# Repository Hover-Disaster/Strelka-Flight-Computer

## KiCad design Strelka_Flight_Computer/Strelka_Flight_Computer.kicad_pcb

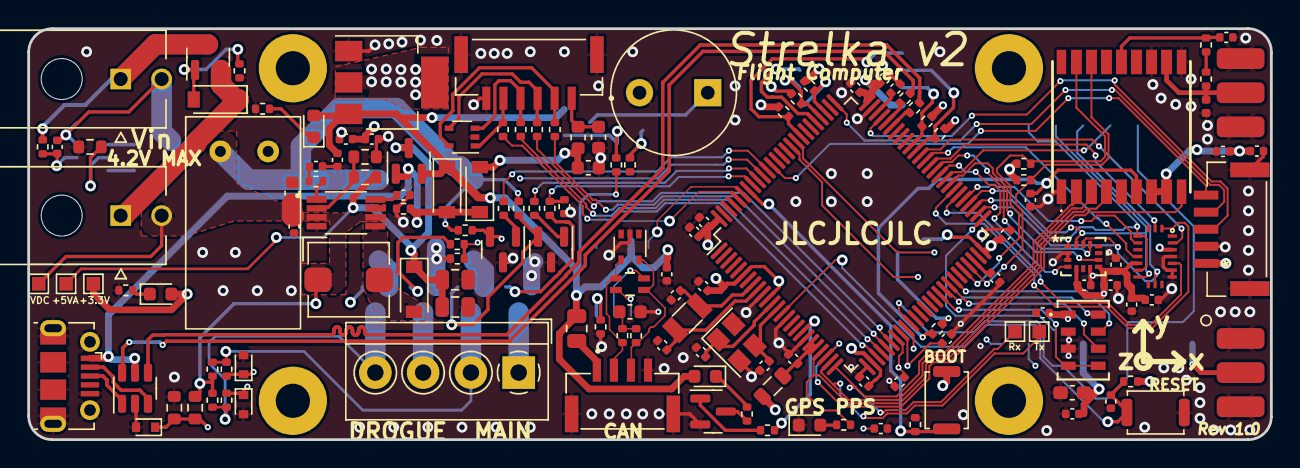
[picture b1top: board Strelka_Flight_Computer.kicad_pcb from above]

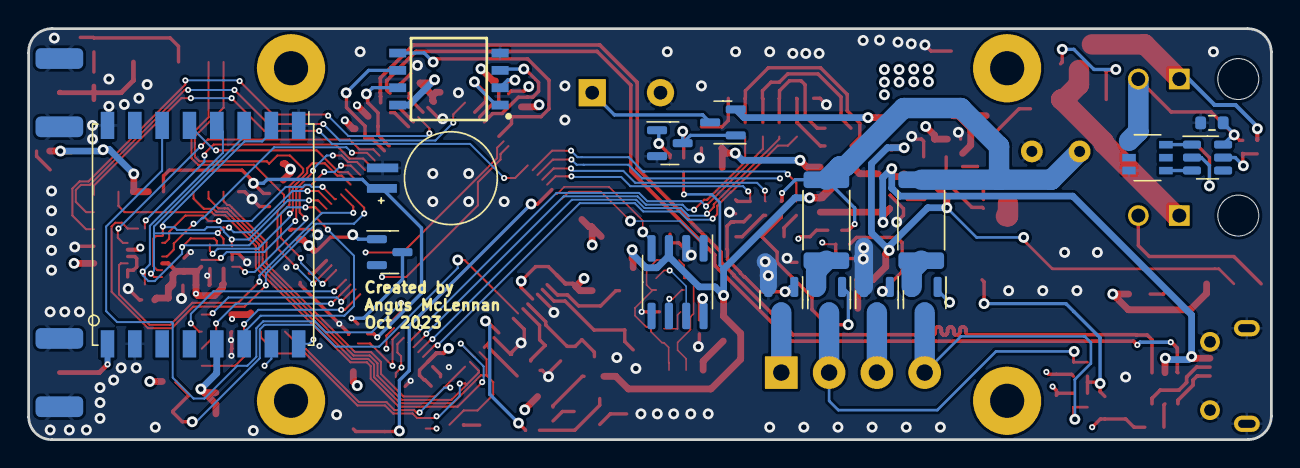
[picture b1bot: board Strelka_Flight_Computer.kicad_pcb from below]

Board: 4 copper layers, 91.0 x 30.1 mm, 165 parts (16 on the bottom side), 124 nets.

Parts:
AE1, AE2: Antenna_Shield; STA-10201
BT2: MS621FE-FL11E; BAT_MS621FE-FL11E
BZ3: Buzzer; HNB09A05
C1, C2, C4, C5, C6, C10, C28, C29, C30, C31, C39, C48, C50, C52, C53, C54, C60, C61, C66: 100n; C_0402_1005Metric
C3, C7, C8, C40: 10u; C_0402_1005Metric
C9, C12, C13: 10n; C_0402_1005Metric
C11: 10u; C_0603_1608Metric_Pad1.08x0.95mm_HandSolder
C14, C55: 22u; C_0805_2012Metric
C15: 4.7n; C_0603_1608Metric
C26, C27: 2.2u; C_0603_1608Metric
C37: NC; C_0402_1005Metric
C38: 4.7u; C_0402_1005Metric
C41: 1500u; ULR158M0JF1ARR
C46: 22u; C_0603_1608Metric
C47, C49: 1u; C_0402_1005Metric
C51: 2.2n; C_0402_1005Metric
C62, C63: 18p; C_0402_1005Metric
C64, C65: 15p; C_0402_1005Metric
C67, C68: 2.2u; C_0402_1005Metric
D1, D2, D4: B5819W; D_SOD-123
D3, D5, D13: BZT52C3V6T; D_SOD-523
D6, D7: SP0504BAJT; SOT-353_SC-70-5
D10: ESD9B3.3ST5G; D_0402_1005Metric
D11: BAT54C; SOT-23
D12: LED_GREEN; LED_0603_1608Metric
D14: DSK34; D_SOD-123
D18: RED LED; LED_0603_1608Metric
D19: YELLOW LED; LED_0603_1608Metric
D20: BLUE LED; LED_0603_1608Metric
F1: MF-PSHT035KX-2; R_0805_2012Metric
FB2: BLM18PG221SN1D; L_0603_1608Metric
FB3: HZ1005K182TFB03; R_0402_1005Metric
FL1: 744231121; CHIP_31121_WRE
H1, H2, H3, H4: MountingHole; MountingHole_2.5mm_Pad
IC1: XTSD04GLGEAG; SON127P800X600X95-8N
IC2: MAX-M10S-00B; MAXM10S00B
J2: Conn_01x04; JST_SM04B-GHS-TB(LF)(SN)-
J3: DB125-3.5-4P-GN-S; TerminalBlock_4Ucon_1x04_P3.50mm_Horizontal
J4: SM06B-GHS-TB(LF)(SN); JST_SM06B-GHS-TB(LF)(SN)
J6: USB_B_Micro; USB_Micro-B_Molex-105017-0001
J7: Conn_01x02; MOLEX_43045-0200
J8: Conn_01x07; SM05B-GHS-TBLFSN
L2: 6u; L_Bourns_SRP5030T
L4: 10u; L_0805_2012Metric
MOSFET1: DMG6968UDM-7
Q1, Q2: CJK2333; SOT-23
Q4, Q9, Q17: AO3401A; SOT-23
Q5, Q10: AP2300; SOT-23
Q6, Q11: MMBT2222; SOT-23
Q15, Q16: AO3400A; SOT-23
R1: 0R; R_0603_1608Metric
R2, R3, R4, R5, R6, R8, R81: 100k; R_0402_1005Metric
R7: 330R; R_0402_1005Metric
R9: 2.7k; R_0603_1608Metric
R10, R11, R12, R16, R17, R31, R51, R56, R57, R74, R77, R78, R80: 1k; R_0402_1005Metric
R13, R26: 60R4; R_0402_1005Metric
R14, R15, R61, R75, R79, R86, R87: 10k; R_0402_1005Metric
R18, R19, R21, R65, R76: 33R; R_0402_1005Metric
R20, R23, R24, R25, R35: 47k; R_0402_1005Metric
R22, R84: 10R; R_0402_1005Metric
R27, R47: 2R; R_2512_6332Metric
R55: 0R; R_0402_1005Metric
R59: 13k; R_0603_1608Metric
R60: 47k; R_0603_1608Metric
R62: 82k; R_0603_1608Metric
R63: 27k; R_0603_1608Metric
SW1: SW_DIP_x01; MOLEX_43045-0200
SW6, SW7: TS-1185-C-A-A-A; SW_Push_SPST_NO_Alps_SKRK
TP1, TP3, TP4, TP9, TP10: TestPoint; TestPoint_Pad_1.0x1.0mm
U1: ASM330LHHXTR; QFN_LHHXTR_STM
U2: AP9101CK6; SOT-23-6
U3: AMS1117-3.3; SOT-223-3_TabPin2
U4: RFM95W-915S2; HOPERF_RFM9XW_SMD
U5: MCP2551-I-SN; SOIC-8_3.9x4.9mm_P1.27mm
U6: STM32H743VITx; LQFP-100_14x14mm_P0.5mm
U8: USBLC6-2SC6; SOT-23-6
U11: BMX055
U12: MS561101BA03-50
U16: TPS61085DGKR; SOP65P490X110-8N
Y5: Q13FC1350000400; Crystal_SMD_3215-2Pin_3.2x1.5mm
Y6: X1E0000210834; Crystal_SMD_SeikoEpson_TSX3225-4Pin_3.2x2.5mm

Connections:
+3.3V: C2.1, C3.1, C4.1, C7.1, C8.1, C10.1, C11.1, C28.1, C29.1, C30.1, C31.1, C39.1, C40.1, C50.1, C52.1, C53.1, C54.1, C60.1, C61.1, D11.1, D19.2 (A), IC1.8 (VDD,_POWER_SUPPLY), IC2.7 (V_IO), IC2.8 (VCC), J8.1, L4.1, R20.1, R23.1, R24.1, R25.1, R35.1, R79.2, R86.2, R87.2, SW6.2, TP4.1, U1.5 (Vdd_IO), U1.8 (Vdd), U3.2 (VO), U4.13 (3.3V), U6.6 (VBAT), U6.11 (VDD), U6.27 (VDD), U6.50 (VDD), U6.75 (VDD), U6.100 (VDD), U11.3 (VDD), U11.13 (VDDIO), U12.1 (VDD)
+5V: C1.1, C5.1, D2.1 (K), D18.2 (A), D20.2 (A), F1.1, Q2.2 (S), Q17.2 (S), R81.2, U3.3 (VI), U5.3 (VDD)
+5VA: C14.1, C55.1, D14.1 (K), Q2.3 (D), R62.2, TP3.1
+5VD: C26.2, D4.2 (A), FB2.2
+BATT: J7.1, Q1.3 (D), R7.1
-BATT: C6.2, J7.2, MOSFET1.1 (S1), R1.1, U2.6 (VSS)
/915MHz_Radio/CS_RF: U4.5 (NSS), U6.59 (PD12)
/915MHz_Radio/IO0_RF: U4.14 (DIO0), U6.51 (PB12)
/915MHz_Radio/IO1_RF: U4.15 (DIO1), U6.84 (PD3)
/915MHz_Radio/IO2_RF: U4.16 (DIO2), U6.85 (PD4)
/915MHz_Radio/LoRa_Sig: AE1.1 (A), U4.9 (ANT)
/915MHz_Radio/RESET_RF: U4.6 (RESET), U6.35 (PB1)
/915MHz_Radio/SPI_CLK: U1.13 (SCL), U4.4 (SCK), U6.52 (PB13), U11.9 (SCX)
/915MHz_Radio/SPI_MISO: U1.1 (SDO/SA0), U4.2 (MISO), U6.53 (PB14), U11.12 (SDO2), U11.17 (SDO1)
/915MHz_Radio/SPI_MOSI: U1.14 (SDA), U4.3 (MOSI), U6.54 (PB15), U11.11 (SDX)
/Actuators/D+: J3.4, Q4.3 (D), R14.2, R16.2
/Actuators/D-: J3.3, Q5.3 (D)
/Actuators/DROGUE_CONT: C12.1, D3.1 (K), R14.1, U6.33 (PC5)
/Actuators/DROGUE_H: R10.1, U6.90 (PB4)
/Actuators/DROGUE_L: R5.2, R31.1, U6.91 (PB5)
/Actuators/EXT_SPI_CS: R21.2, U6.28 (PA4)
/Actuators/EXT_SPI_MISO: R65.2, U6.30 (PA6)
/Actuators/EXT_SPI_MOSI: R18.2, U6.31 (PA7)
/Actuators/EXT_SPI_SCK: R19.2, U6.29 (PA5)
/Actuators/Ematch_Drogue1/em+: Q4.2 (S), R27.2
/Actuators/Ematch_Main/em+: Q9.2 (S), R47.2
/Actuators/M+: J3.2, Q9.3 (D), R15.2, R17.2
/Actuators/M-: J3.1, Q10.3 (D)
/Actuators/MAIN_CONT: C13.1, D5.1 (K), R15.1, U6.34 (PB0)
/Actuators/MAIN_H: R11.1, U6.92 (PB6)
/Actuators/MAIN_L: R6.2, R51.1, U6.93 (PB7)
/Data_Interfaces/CANH: FL1.4, U5.7 (CANH)
/Data_Interfaces/CANL: FL1.2, U5.6 (CANL)
/Data_Interfaces/CAN_+: D7.4 (K), FL1.3, J2.2, R13.1
/Data_Interfaces/CAN_-: D7.5 (K), FL1.1, J2.3, R26.2
/Data_Interfaces/CAN_RXD: U5.4 (RXD), U6.95 (PB8)
/Data_Interfaces/CAN_TXD: U5.1 (TXD), U6.96 (PB9)
/Data_Interfaces/USB2_D+: J6.3 (D+), U8.1 (I/O1)
/Data_Interfaces/USB2_D-: J6.2 (D-), U8.3 (I/O2)
/Data_Interfaces/USB_D+: R22.2, U8.6 (I/O1)
/Data_Interfaces/USB_D-: R84.2, U8.4 (I/O2)
/Data_Interfaces/V_CAN: F1.2, J2.1
/Data_Interfaces/tap: C15.1, R13.2, R26.1
/Data_Logging/CLK: IC1.3 (CLK,_CLOCK_SIGNAL), U6.80 (PC12)
/Data_Logging/CMD: IC1.5 (CMD,_COMMAND_SIGNAL), R35.2, U6.83 (PD2)
/Data_Logging/SD0: IC1.6 (SD0,_I/O_PIN), R25.2, U6.65 (PC8)
/Data_Logging/SD1: IC1.7 (SD1,_I/O_PIN), R24.2, U6.66 (PC9)
/Data_Logging/SD2: IC1.1 (SD2,_I/O_PIN), R23.2, U6.78 (PC10)
/Data_Logging/SD3: IC1.2 (SD3,_I/O_PIN), R20.2, U6.79 (PC11)
/Power/BATT_VOLT: C9.1, D13.1 (K), R59.1, R60.2, U6.32 (PC4)
/Power/SW_IN: D1.1 (K), Q1.2 (S), SW1.1
/STM32H743/BOOT0: R75.2, SW6.1, U6.94 (BOOT0)
/STM32H743/D+: R22.1, U6.71 (PA12)
/STM32H743/D-: R84.1, U6.70 (PA11)
/STM32H743/EXTI6: U6.63 (PC6), U11.14 (INT3)
/STM32H743/EXTI7: U6.64 (PC7), U11.2 (DRDYM)
/STM32H743/EXTI13: U1.4 (INT1), U6.60 (PD13)
/STM32H743/EXTI14: U1.9 (INT2), U6.61 (PD14)
/STM32H743/EXTI15: U6.62 (PD15), U11.19 (INT1)
/STM32H743/GPS_RST: IC2.9 (RESET_N), U6.23 (PA1)
/STM32H743/I2C2_SCL: IC2.17 (SCL), R86.1, U6.46 (PB10)
/STM32H743/I2C2_SDA: IC2.16 (SDA), R87.1, U6.47 (PB11)
/STM32H743/INDICATOR_LED: R74.2, U6.18 (PC3_C)
/STM32H743/NRST: C49.1, R79.1, SW7.2, U6.14 (NRST)
/STM32H743/OSC32_IN: C62.1, U6.8 (PC14), Y5.1
/STM32H743/OSC32_OUT: C63.1, U6.9 (PC15), Y5.2
/STM32H743/OSC_IN: C64.1, U6.12 (PH0), Y6.1
/STM32H743/OSC_OUT: C65.1, U6.13 (PH1), Y6.3
/STM32H743/SPI2_NSS1: U6.55 (PD8), U11.16 (CSB1)
/STM32H743/SPI2_NSS2: U6.56 (PD9), U11.5 (CSB2)
/STM32H743/SPI2_NSS3: U6.57 (PD10), U11.20 (CSB3)
/STM32H743/SPI2_NSS4: U1.12 (CS), U6.58 (PD11)
/STM32H743/SPI4_MISO: U6.43 (PE13), U12.6 (SDO)
/STM32H743/SPI4_MOSI: U6.44 (PE14), U12.7 (SDI/SDA)
/STM32H743/SPI4_NSS: U6.41 (PE11), U12.4 (CSB), U12.5 (CSB)
/STM32H743/SPI4_SCK: U6.42 (PE12), U12.8 (SCLK)
/STM32H743/SWCLK: J8.4, U6.76 (PA14)
/STM32H743/SWDIO: J8.3, U6.72 (PA13)
/STM32H743/SWO: J8.5, U6.89 (PB3)
/STM32H743/USART2_RX: IC2.2 (TXD), TP9.1, U6.25 (PA3)
/STM32H743/USART2_TX: IC2.3 (RXD), TP10.1, U6.24 (PA2)
/STM32H743/VDDA: C66.1, L4.2, U6.20 (VREF+), U6.21 (VDDA)
/Sensors/MAX-M10S-00B/PPS: IC2.4 (TIMEPULSE), R57.1, U6.22 (PA0)
/Sensors/MAX-M10S-00B/RF_IN: AE2.1 (A), D10.2 (A2), FB3.1, IC2.11 (RF_IN)
/Sensors/MAX-M10S-00B/VCC_RF: C37.1, IC2.14 (VCC_RF), R55.1
/Sensors/MAX-M10S-00B/V_BKCP: BT2.+ (r~), C38.1, IC2.6 (V_BCKP), R56.1
GND: AE1.2 (Shield), AE2.2 (Shield), BT2.-, BZ3.2 (+), C1.2, C2.2, C3.2, C4.2, C5.2, C7.2, C8.2, C9.2, C10.2, C11.2, C12.2, C13.2, C14.2, C15.2, C26.1, C27.1, C28.2, C29.2, C30.2, C31.2, C37.2, C38.2, C39.2, C40.2, C41.2, C46.2, C47.2, C48.2, C49.2, C50.2, C51.2, C52.2, C53.2, C54.2, C55.2, C60.2, C61.2, C62.2, C63.2, C64.2, C65.2, C66.2, C67.2, C68.2, D3.2 (A), D5.2 (A), D6.2 (A), D7.2 (A), D10.1 (A1), D12.1 (K), D13.2 (A), IC1.4 (VSS,_GROUND), IC2.1 (GND_1), IC2.10 (GND_2), IC2.12 (GND_3), J2.4, J2.5, J2.6, J4.6, J4.S1 (SHIELD), J4.S2 (SHIELD), J6.5 (GND), J6.6 (Shield), J8.2, J8.6, J8.7, MOSFET1.3 (S2), Q5.2 (S), Q6.3 (E), Q10.2 (S), Q11.3 (E), Q15.2 (S), Q16.2 (S), R1.2, R3.1, R5.1, R6.1, R8.1, R9.2, R12.2, R60.1, R63.1, R75.1, R77.1, R78.1, SW7.1, U1.2 (MSDA), U1.3 (MSCL), U1.7 (GND), U3.1 (GND), U4.1 (GND), U4.8 (GND), U4.10 (GND), U5.2 (VSS), U6.10 (VSS), U6.15 (PC0), U6.19 (VSSA), U6.26 (VSS), U6.49 (VSS), U6.74 (VSS), U6.99 (VSS), U8.2 (GND), U11.4 (GNDA), U11.6 (GNDIO), U11.7 (PS), U12.2 (PS), U12.3 (GND), U16.4 (PGND), Y6.2, Y6.4
unnamed: BZ3.1 (-), Q17.3 (D)
unnamed: C27.2, FB2.1, J4.1
unnamed: C51.1, R61.1
unnamed: C67.1, U6.48 (VCAP)
unnamed: C68.1, U6.73 (VCAP)
unnamed: D1.2 (A), Q1.1 (G), R3.2
unnamed: D6.1 (K), J4.5, R21.1
unnamed: D6.3 (K), J4.4, R19.1
unnamed: D6.4 (K), J4.3, R18.1
unnamed: D6.5 (K), J4.2, R65.1
unnamed: D11.3, R56.2
unnamed: D12.2 (A), R57.2
unnamed: D14.2 (A), L2.2, U16.5 (SW)
unnamed: D18.1 (K), R76.2
unnamed: D19.1 (K), R77.2
unnamed: D20.1 (K), R78.2
unnamed: FB3.2, R55.2
unnamed: MOSFET1.6 (G1), U2.1 (DO)
unnamed: MOSFET1.4 (G2), U2.3 (CO)
unnamed: Q4.1 (G), Q6.2 (C), R2.1
unnamed: Q5.1 (G), R31.2
unnamed: Q6.1 (B), R10.2
unnamed: Q10.1 (G), R51.2
unnamed: Q11.1 (B), R11.2
unnamed: Q9.1 (G), Q11.2 (C), R4.1
unnamed: Q15.3 (D), R76.1
unnamed: Q15.1 (G), R74.1
unnamed: Q16.3 (D), Q17.1 (G), R81.1
unnamed: Q16.1 (G), R80.1
unnamed: C6.1, R7.2, U2.5 (VDD)
unnamed: R9.1, U2.2 (VM)
unnamed: R12.1, U5.8 (Rs)
unnamed: R61.2, U16.1 (COMP)
unnamed: R62.1, R63.2, U16.2 (FB)
unnamed: C48.1, U16.8 (SS)
VBUS: D2.2 (A), D4.1 (K), J6.1 (VBUS), Q2.1 (G), R8.2, U8.5 (VBUS)
VDC: C41.1, C46.1, C47.1, L2.1, R2.2, R4.2, R16.1, R17.1, R27.1, R47.1, R59.2, SW1.2, TP1.1, U16.3 (EN), U16.6 (IN), U16.7 (FREQ)

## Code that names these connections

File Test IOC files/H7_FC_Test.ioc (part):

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Mcu.Name=STM32H743VGTx
Mcu.Package=LQFP100
Mcu.UserName=STM32H743VGTx
PA0.GPIOParameters=GPIO_Label
PA0.GPIO_Label=GPS_PPS
PA0.Signal=GPXTI0
PA1.GPIOParameters=GPIO_Label
PA1.GPIO_Label=GPS_RST
PA1.Signal=GPIO_Output
PA11.Mode=Device_Only
PA11.Signal=USB_OTG_FS_DM
PA12.Mode=Device_Only
PA12.Signal=USB_OTG_FS_DP
PA13\ (JTMS/SWDIO).Mode=Trace_Asynchronous_SW
PA13\ (JTMS/SWDIO).Signal=DEBUG_JTMS-SWDIO
PA14\ (JTCK/SWCLK).Mode=Trace_Asynchronous_SW
PA14\ (JTCK/SWCLK).Signal=DEBUG_JTCK-SWCLK
PA2.Mode=Asynchronous
PA2.Signal=USART2_TX
PA3.Mode=Asynchronous
PA3.Signal=USART2_RX
PA4.Mode=NSS_Signal_Hard_Output
PA4.Signal=SPI1_NSS
PA5.Mode=Full_Duplex_Master
PA5.Signal=SPI1_SCK
PA6.Mode=Full_Duplex_Master
PA6.Signal=SPI1_MISO
PA7.Mode=Full_Duplex_Master
PA7.Signal=SPI1_MOSI
PB0.GPIOParameters=GPIO_Label
PB0.GPIO_Label=MAIN_CONT
PB0.Signal=ADCx_INP9
PB1.GPIOParameters=GPIO_Label
PB1.GPIO_Label=RESET_RF
PB1.Signal=GPIO_Output
PB10.Mode=I2C
PB10.Signal=I2C2_SCL
PB11.Mode=I2C
PB11.Signal=I2C2_SDA
PB12.GPIOParameters=GPIO_Label
PB12.GPIO_Label=IO0_RF
PB12.Signal=GPXTI12
PB13.Mode=Full_Duplex_Master
PB13.Signal=SPI2_SCK
PB14.Mode=Full_Duplex_Master
PB14.Signal=SPI2_MISO
PB15.Mode=Full_Duplex_Master
PB15.Signal=SPI2_MOSI
PB3\ (JTDO/TRACESWO).Mode=Trace_Asynchronous_SW
PB3\ (JTDO/TRACESWO).Signal=DEBUG_JTDO-SWO
PB4\ (NJTRST).GPIOParameters=GPIO_Label
PB4\ (NJTRST).GPIO_Label=DROGUE_H
PB4\ (NJTRST).Signal=GPIO_Output
PB5.GPIOParameters=GPIO_Label
PB5.GPIO_Label=DROGUE_L
PB5.Signal=GPIO_Output
PB6.GPIOParameters=GPIO_Label
PB6.GPIO_Label=MAIN_H
PB6.Signal=GPIO_Output
PB7.GPIOParameters=GPIO_Label
PB7.GPIO_Label=MAIN_L
PB7.Signal=GPIO_Output
PB8.Mode=FDCAN_Activate
PB8.Signal=FDCAN1_RX
PB9.Mode=FDCAN_Activate
PB9.Signal=FDCAN1_TX
PC0.GPIOParameters=GPIO_Label
PC0.GPIO_Label=SD_Det
PC0.Signal=GPIO_Input
PC10.Mode=SD_4_bits_Wide_bus
PC10.Signal=SDMMC1_D2
PC11.Mode=SD_4_bits_Wide_bus
PC11.Signal=SDMMC1_D3
PC12.Mode=SD_4_bits_Wide_bus
PC12.Signal=SDMMC1_CK
PC14-OSC32_IN\ (OSC32_IN).Mode=LSE-External-Oscillator
PC14-OSC32_IN\ (OSC32_IN).Signal=RCC_OSC32_IN
PC15-OSC32_OUT\ (OSC32_OUT).Mode=LSE-External-Oscillator
PC15-OSC32_OUT\ (OSC32_OUT).Signal=RCC_OSC32_OUT
PC3_C.GPIOParameters=GPIO_Label
PC3_C.GPIO_Label=INDICATOR
PC3_C.Signal=GPIO_Output
PC4.GPIOParameters=GPIO_Label
PC4.GPIO_Label=BATT_SENSE
PC4.Signal=ADCx_INP4
PC5.GPIOParameters=GPIO_Label
PC5.GPIO_Label=DROGUE_CONT
PC5.Signal=ADCx_INP8
PC6.Signal=GPXTI6
PC7.Signal=GPXTI7
PC8.Mode=SD_4_bits_Wide_bus
PC8.Signal=SDMMC1_D0
PC9.Mode=SD_4_bits_Wide_bus
PC9.Signal=SDMMC1_D1
PD10.Signal=GPIO_Output
PD11.Signal=GPIO_Output
PD12.Signal=GPIO_Output
PD13.Signal=GPXTI13
PD14.Signal=GPXTI14
PD15.Signal=GPXTI15
PD2.Mode=SD_4_bits_Wide_bus
PD2.Signal=SDMMC1_CMD
PD3.Signal=GPXTI3
PD8.Signal=GPIO_Output
PD9.Signal=GPIO_Output
PE11.Mode=NSS_Signal_Hard_Output
PE11.Signal=SPI4_NSS
PE12.Mode=Full_Duplex_Master
PE12.Signal=SPI4_SCK
PE13.Mode=Full_Duplex_Master
PE13.Signal=SPI4_MISO
PE14.Mode=Full_Duplex_Master
PE14.Signal=SPI4_MOSI
PH0-OSC_IN\ (PH0).Mode=HSE-External-Oscillator
PH0-OSC_IN\ (PH0).Signal=RCC_OSC_IN
PH1-OSC_OUT\ (PH1).Mode=HSE-External-Oscillator
PH1-OSC_OUT\ (PH1).Signal=RCC_OSC_OUT
RCC.HSE_VALUE=48000000
RCC.SYSCLKFreq_VALUE=480000000
RCC.SYSCLKSource=RCC_SYSCLKSOURCE_PLLCLK
board=custom

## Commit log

2023-10-09 Added pcb files
2023-10-09 Started design for V2
2023-10-10 Changes main processor to h4745
2023-10-11 Started component placement
2023-10-12 Changed design rules
2023-10-13 Routing starting
2023-10-14 Continued routing
2023-10-15 Routing complete
2023-10-16 Created BOM
2023-10-16 Started BOM
2023-10-17 Adjusted master bom
2023-10-17 Adjusted stackup to suit jlc standard stackups
2023-10-19 Via stitched
2023-10-21 Added solder paste to BOM
2023-10-21 Adjusted bom available items
2023-10-25 Added lp filter caps to adc signals
2023-10-29 Added LCSC mpn to all relevent parts
2023-10-30 Completely exported to JLC
2023-11-07 Finalised BOM and sent order:
2023-12-13 Adj to BOM
2023-12-13 Adjusted changes after jlc tech team review
2023-12-13 Accepted all incoming changes
2024-06-03 Updated errata list
2025-02-18 Adjusted errata list
2025-04-02 Added to errata list
2025-05-10 Added note to errata

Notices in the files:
parts and their libraries:
Copyright 2016 Accelerated Designs. All rights reserved.
